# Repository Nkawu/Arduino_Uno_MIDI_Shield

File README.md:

# Arduino Uno MIDI Shield

Follow my [Hackaday Project Page](http://hackaday.io/project/4741-organ-pedalboard-midi-conversion)!

This project originated during the conversion of an old AGO spec pipe organ pedalboard to MIDI in order to be used with
[Hauptwerk](https://www.hauptwerk.com) virtual organ software. 

The shield uses 4 daisy chained CD4021 shift registers to read 32 reed switches installed on the pedalboard. The Arduino Uno reads the shift registers and then sends MIDI notes via [Hiduino](https://github.com/ddiakopoulos/hiduino) firmware flashed to the Uno's Atmel ATmega16U2. The Hiduino firmware makes the Arduino Uno appear as a class-compliant USB-MIDI device.

The project contains: 
* Eagle CAD files for an Arduino Uno R3 shield
* Arduino sketch

**NOTE:** This is still a work in progress. I've breadboarded the circuit with a single CD4021 which works perfectly, but I have yet to daisy chain multiple CD4021s on the breadboard. When that has been done I'll have PCBs made at [OSHPark](https://oshpark.com)

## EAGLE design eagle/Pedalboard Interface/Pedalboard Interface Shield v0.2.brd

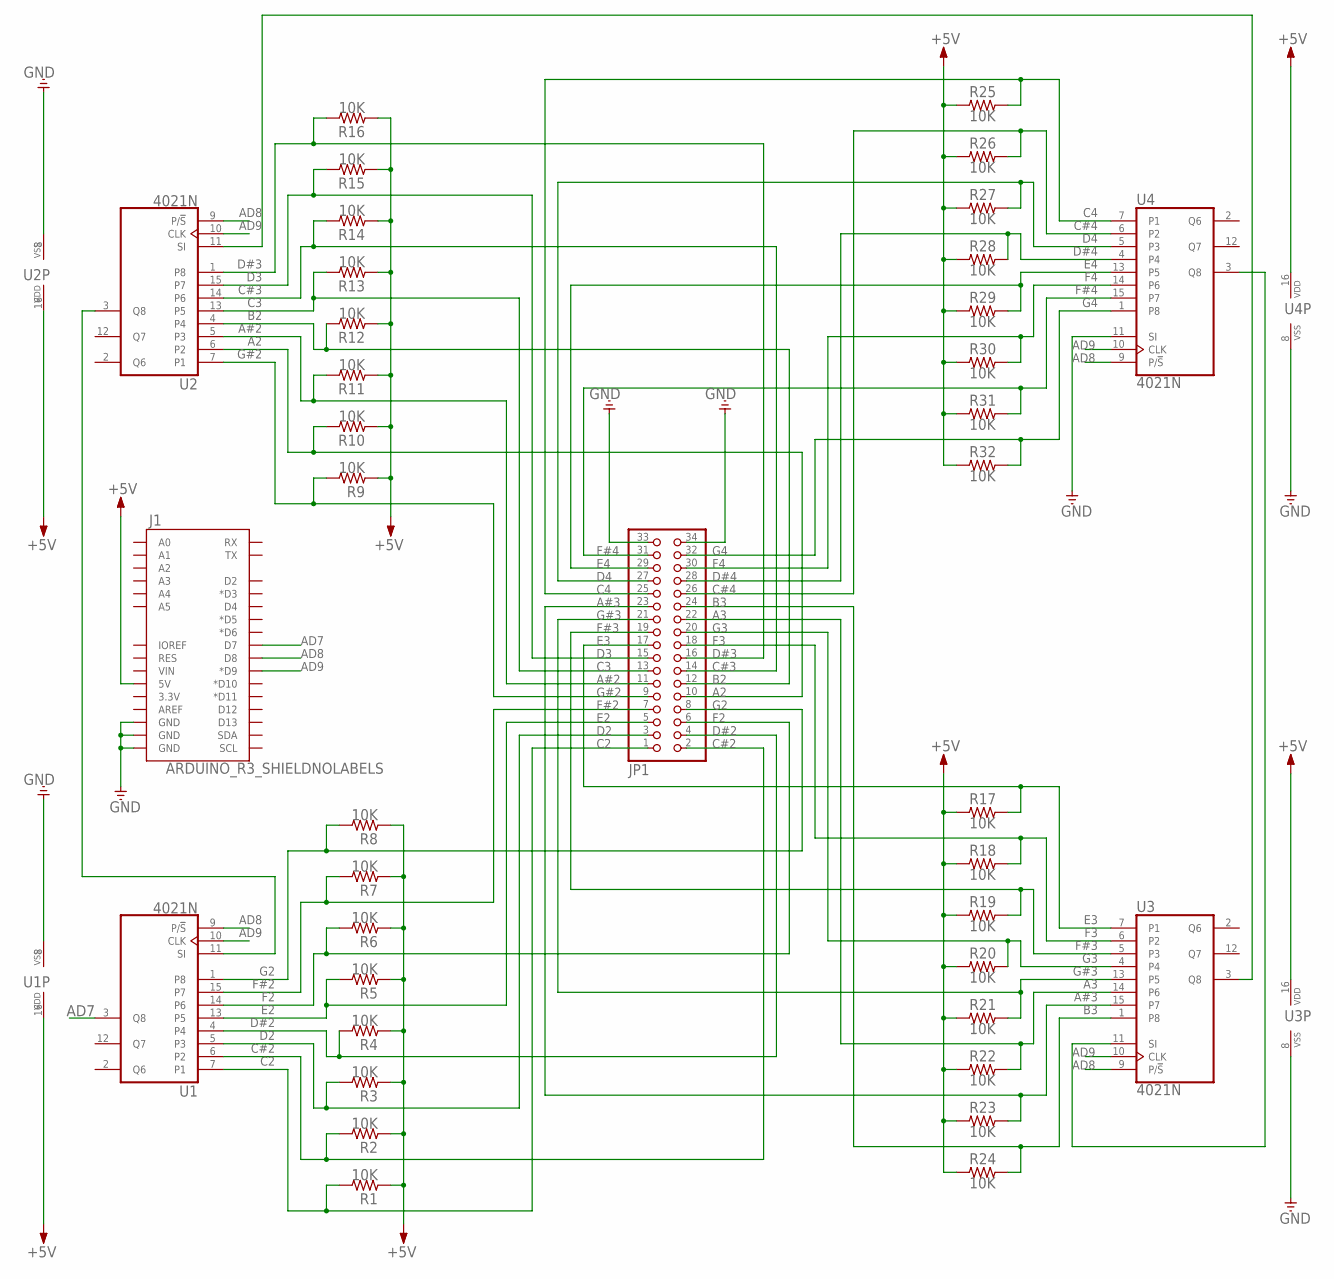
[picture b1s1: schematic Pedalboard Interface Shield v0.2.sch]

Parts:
J1: ARDUINO_R3_SHIELDNOLABELS; UNO_R3_SHIELD_NOLABELS
JP1: PINHD-2X17; 2X17
R1, R2, R3, R4, R5, R6, R7, R8, R9, R10, R11, R12, R13, R14, R15, R16, R17, R18, R19, R20, R21, R22, R23, R24, R25, R26, R27, R28, R29, R30, R31, R32: 10K; 0207/2V
U1, U2, U3, U4: 4021N; DIL16

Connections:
+5V: J1.5V, R1.1, R2.1, R3.1, R4.1, R5.1, R6.1, R7.1, R8.1, R9.1, R10.1, R11.1, R12.1, R13.1, R14.1, R15.1, R16.1, R17.1, R18.1, R19.1, R20.1, R21.1, R22.1, R23.1, R24.1, R25.1, R26.1, R27.1, R28.1, R29.1, R30.1, R31.1, R32.1, U1.16 (VDD), U2.16 (VDD), U3.16 (VDD), U4.16 (VDD)
A2: JP1.10, R10.2, U2.6 (P2)
A3: JP1.22, R22.2, U3.14 (P6)
A#2: JP1.11, R11.2, U2.5 (P3)
A#3: JP1.23, R23.2, U3.15 (P7)
AD7: J1.D7, U1.3 (Q8)
AD8: J1.D8, U1.9 (P/!S), U2.9 (P/!S), U3.9 (P/!S), U4.9 (P/!S)
AD9: J1.D9 (*D9), U1.10 (CLK), U2.10 (CLK), U3.10 (CLK), U4.10 (CLK)
B2: JP1.12, R12.2, U2.4
B3: JP1.24, R24.2, U3.1 (P8)
C2: JP1.1, R1.2, U1.7 (P1)
C3: JP1.13, R13.2, U2.13 (P5)
C4: JP1.25, R25.2, U4.7 (P1)
C#2: JP1.2, R2.2, U1.6 (P2)
C#3: JP1.14, R14.2, U2.14 (P6)
C#4: JP1.26, R26.2, U4.6 (P2)
D2: JP1.3, R3.2, U1.5 (P3)
D3: JP1.15, R15.2, U2.15 (P7)
D4: JP1.27, R27.2, U4.5 (P3)
D#2: JP1.4, R4.2, U1.4
D#3: JP1.16, R16.2, U2.1 (P8)
D#4: JP1.28, R28.2, U4.4
E2: JP1.5, R5.2, U1.13 (P5)
E3: JP1.17, R17.2, U3.7 (P1)
E4: JP1.29, R29.2, U4.13 (P5)
F2: JP1.6, R6.2, U1.14 (P6)
F3: JP1.18, R18.2, U3.6 (P2)
F4: JP1.30, R30.2, U4.14 (P6)
F#2: JP1.7, R7.2, U1.15 (P7)
F#3: JP1.19, R19.2, U3.5 (P3)
F#4: JP1.31, R31.2, U4.15 (P7)
G2: JP1.8, R8.2, U1.1 (P8)
G3: JP1.20, R20.2, U3.4
G4: JP1.32, R32.2, U4.1 (P8)
G#2: JP1.9, R9.2, U2.7 (P1)
G#3: JP1.21, R21.2, U3.13 (P5)
GND: J1.GND@0 (GND), J1.GND@1 (GND), J1.GND@2 (GND), JP1.33, JP1.34, U1.8 (VSS), U2.8 (VSS), U3.8 (VSS), U4.8 (VSS), U4.11 (SI)
unnamed: U2.11 (SI), U3.3 (Q8)
unnamed: U3.11 (SI), U4.3 (Q8)
unnamed: U1.11 (SI), U2.3 (Q8)

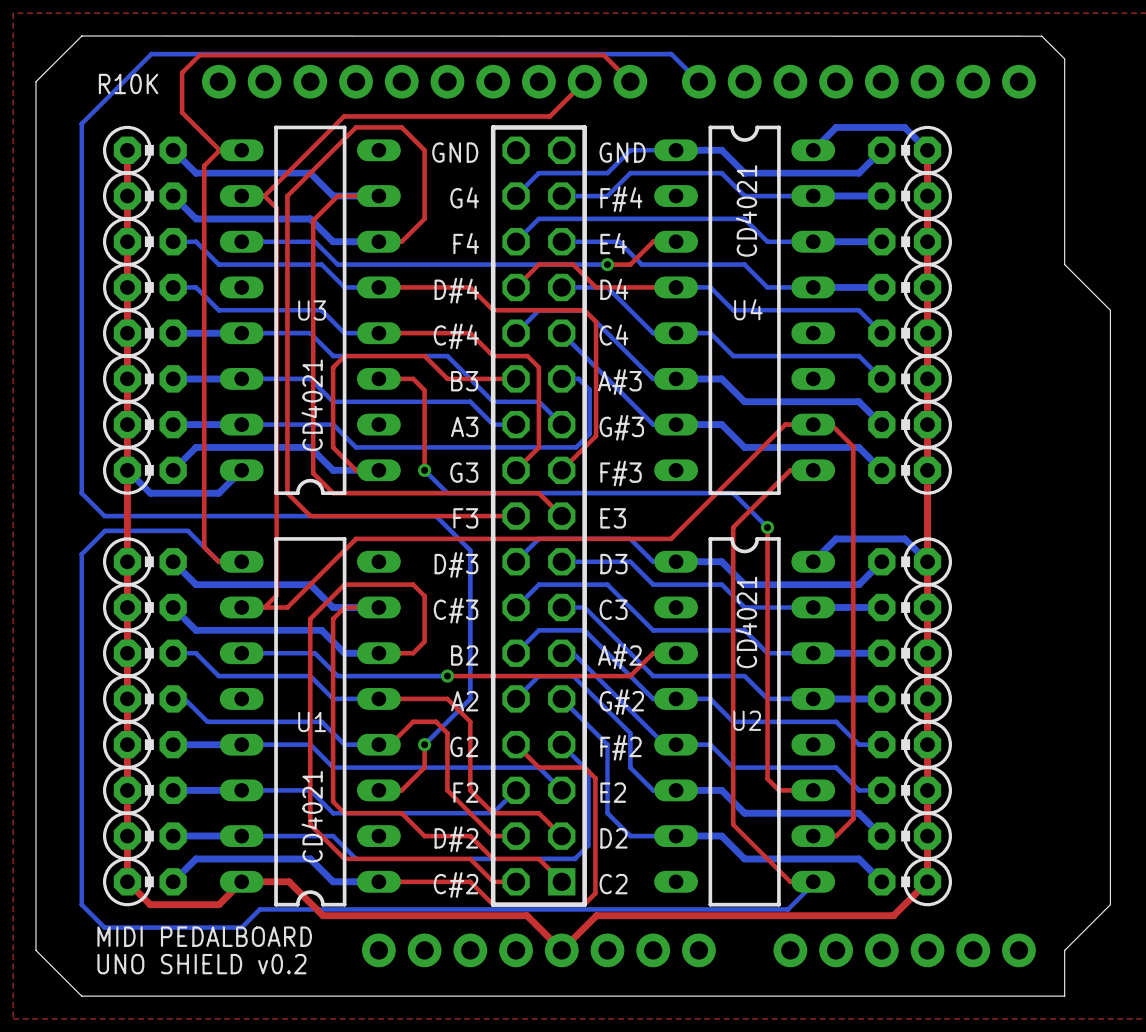
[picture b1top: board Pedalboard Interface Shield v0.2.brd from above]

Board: 2 copper layers, 59.7 x 53.3 mm, 38 parts (0 on the bottom side), 40 nets.

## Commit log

2015-03-13 Added Eagle & Arduino files

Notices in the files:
parts and their libraries:
SparkFun-Boards: Licensing: Creative Commons ShareAlike 4.0 International - https://creativecommons.org/licenses/by-sa/4.0
rc-master: Copyright (C) 2007-2008, Bob Starr
supply1: Copyright (C) 2007, Bob Starr
